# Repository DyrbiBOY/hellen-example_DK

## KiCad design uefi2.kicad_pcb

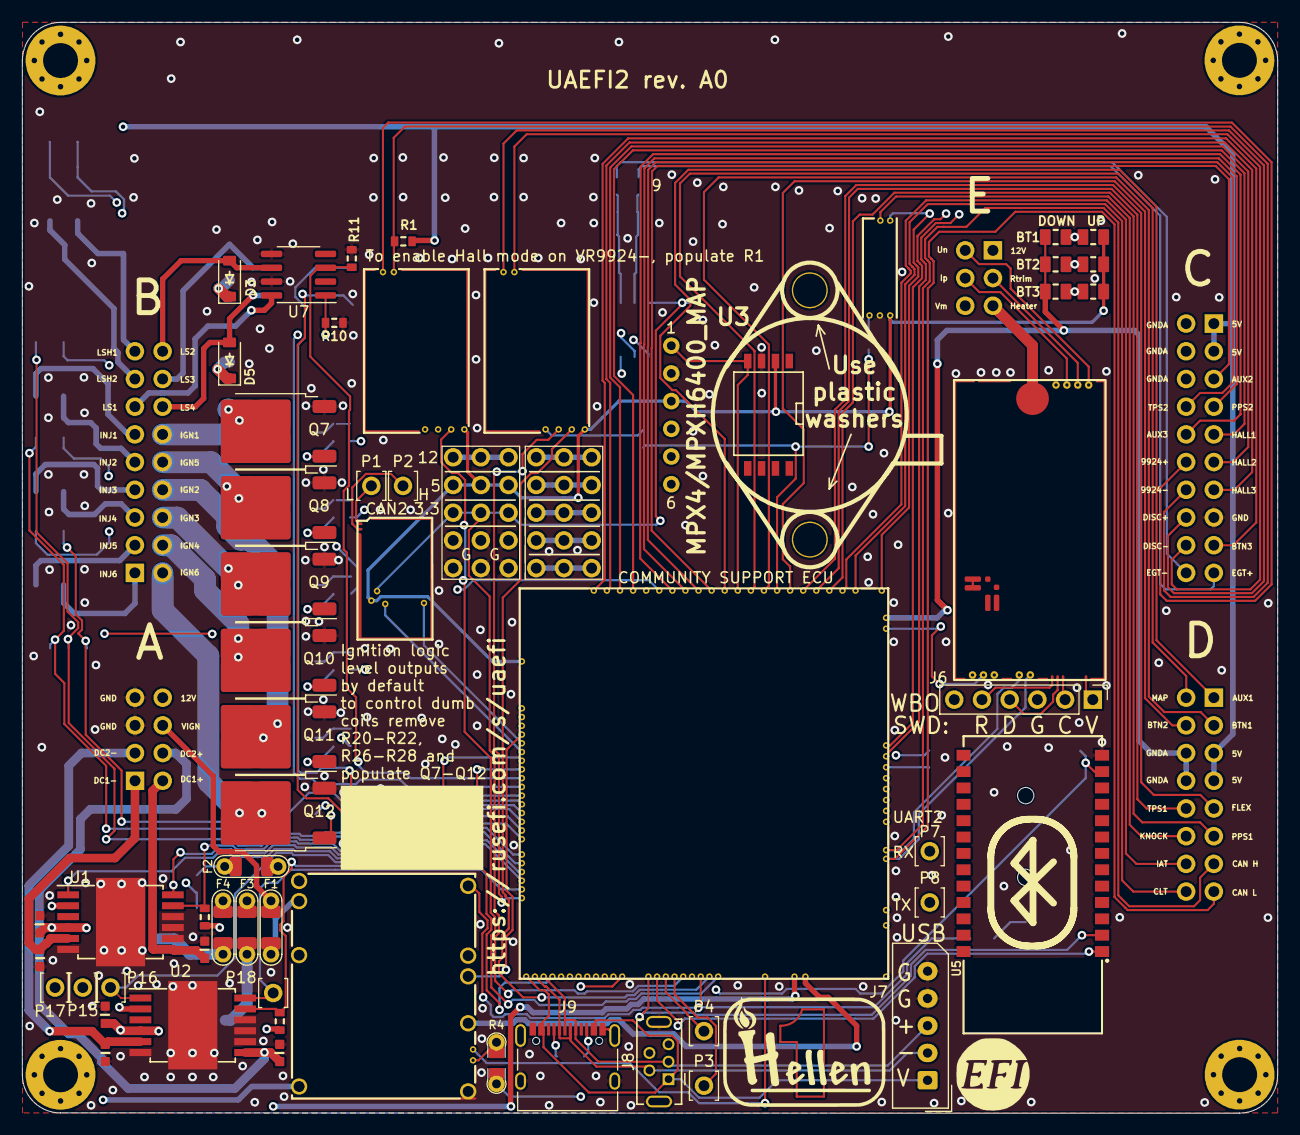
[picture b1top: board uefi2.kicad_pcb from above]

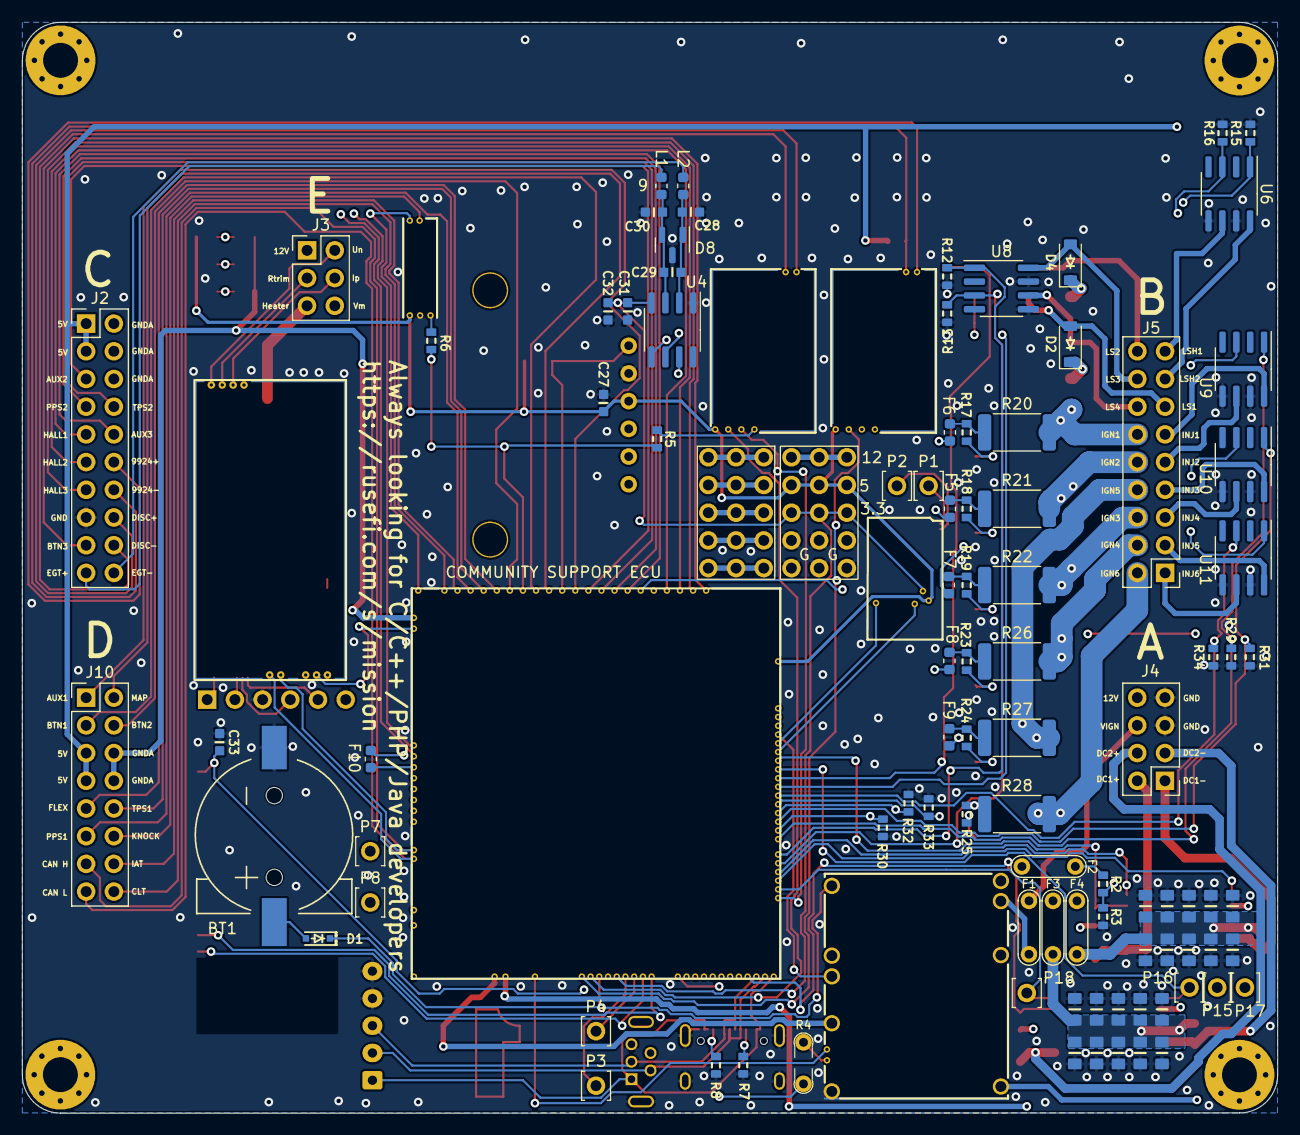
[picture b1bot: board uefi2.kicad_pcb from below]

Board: 4 copper layers, 115.1 x 100.0 mm, 143 parts (79 on the bottom side), 145 nets.

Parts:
BT1: CR1220; CR1220-2
C1, C2, C3, C4, C5, C6, C7, C8, C9, C10, C14, C15, C16, C17, C18, C19, C20, C21, C22, C23: 10u; C0805
C11, C24, C27, C29, C31, C33: 100n; C0603
C12, C13, C25, C26, C28, C30: 10n; C0603
C32: 1u; C0603
D1: 1N4148WS; SOD-323
D2, D3, D4, D5: B5819W; SOD-123
D8: NUP2105L; SOT-23
F1, F2, F3, F4: 12H1500D; PAD-1206-PAD
F5, F6, F7, F8, F9, F10: 50mA; Fuse_0603_1608Metric
G1: RUSEFI_LOGO; rusefi_logo
G2: LOGO
G3, G4: PROTO_AREA
H1, H1#2, H1#3, H2: M3; MountingHole_3.2mm_M3_Pad_Via
J2: Conn_02x10_Odd_Even; PinHeader_2x10_P2.54mm_Vertical
J3: Conn_02x03_Odd_Even; PinHeader_2x03_P2.54mm_Vertical
J4: Conn_02x04_Odd_Even; PinHeader_2x04_P2.54mm_Vertical
J5: Conn_02x09_Odd_Even; PinHeader_2x09_P2.54mm_Vertical
J6: Conn_01x06; PinHeader_1x06_P2.54mm_Vertical
J7: Conn_01x05_Male; Molex_SPOX_5267-05A_1x05_P2.50mm_Vertical
J8: USB_B_Mini; USB-MINI-B-VERTICAL
J9: USB_C
J10: Conn_02x08_Odd_Even; PinHeader_2x08_P2.54mm_Vertical
L1, L2: 470R@100MHz; L_0603_1608Metric
M1: Module-power_12and5V-0.2; power_12and5V
M2: Module-knock-0.2; knock
M3: Module-vr-discrete-0.5; vr-discrete
M4: Module-vr-max9924-0.1; vr-max9924
M5: Module-wbo-0.5; wbo
M6: Module:mega-mcu100/0.3; mega-mcu100
M7: Module-can-0.1; can
P1, P2, P3, P4, P7, P8, P15, P16, P17, P18: Pad; PAD-TH
Q7, Q8, Q9, Q10, Q11, Q12: ISL9V3040D3ST; TO-252-2
R1, R9, R10, R11, R12, R13, R14, R15, R16, R29, R30, R31, R32, R33, R34: 4.7k; R0603
R2: 33k; R0603
R3: 6.8k; R0603
R4: Jumper-Pad-Pad; PAD-0805-PAD
R5, R6: 0; R0603
R7, R8: 5.6k; R0603
R17, R18, R19, R23, R24, R25: 22; R0603
R20, R21, R22, R26, R27, R28: 0; R_2512_6332Metric
R35, R36, R37: 10k; R0805
R38, R39, R40: DNP; R0805
U1, U2: TLE9201SG; Infineon_PG-DSO-12-11
U3: MPX4/MPXH6400_MAP; MPX-4_MAP
U4: MAX31855KASA; SOIC-8_3.9x4.9mm_P1.27mm
U5: JDY-33
U6, U7, U8, U9, U10, U11: VNLD5160TR-E; SOIC-8_3.9x4.9mm_P1.27mm

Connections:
+3.3V: M6.N21 (V33), R9.2, R14.2, U1.2 (VSO), U2.2 (VSO)
+3.3VA: C31.2, C32.2, C33.2, G3.3, G3.8, G3.13, M6.N15 (V33_SWITCHABLE), M7.V2 (CAN_VIO), U4.4 (V_CC), U5.12 (3V3)
+5V: M1.E4 (V5), M6.N22 (VCC)
+5VA: C27.2, G3.4, G3.9, G3.14, M2.E1 (V5A), M3.E4 (V5_IN), M4.E4 (V5_IN), M5.W1 (V5_IN), M6.E1 (V5A_SWITCHABLE), M6.W2 (V5A_SWITCHABLE), M7.V1 (V5), R38.2, R39.2, R40.2, U3.3 (VCC)
+5VP: J2.1, J2.3, J10.5, J10.7, M1.V4 (5VP), R1.1
+12V: F2.1, F3.1, F4.1, J4.8, R2.2
+12V_RAW: D2.1 (K), D3.1 (K), D4.1 (K), D5.1 (K), F2.2, G3.5, G3.10, G3.15, J3.1, M1.V1 (V12_PERM), M1.V3 (V12_RAW)
/12V_KEY: F1.1, J4.6
/ADC3: M6.S15 (IN_KNOCK_(PA2)), R5.2, R6.2
/CAN+: J10.13, M5.W4 (CANH), M6.W11 (CANH)
/CAN-: J10.15, M5.W3 (CANL), M6.W12 (CANL)
/DC1_DIR: M6.E21 (OUT_PWM4_(PC8)), P15.1, U1.1 (DIR)
/DC1_DIS: M6.E8 (SPI2_MISO_(PB14)), R9.1, U1.11 (DIS)
/DC1_PWM: M6.E20 (OUT_PWM3_(PC7)), P17.1, U1.12 (PWM)
/DC2_DIR: M6.E9 (SPI2_MOSI_(PB15)), P16.1, U2.1 (DIR)
/DC2_DIS: M6.N4 (USBID_(PA10)), R14.1, U2.11 (DIS)
/DC2_PWM: M6.E22 (OUT_PWM5_(PC9)), P18.1, U2.12 (PWM)
/DC Driver 1/PWR: C1.2, C2.2, C3.2, C4.2, C5.2, C6.2, C7.2, C8.2, C9.2, C10.2, C11.2, F4.2, U1.4 (VS)
/DC Driver 2/PWR: C14.2, C15.2, C16.2, C17.2, C18.2, C19.2, C20.2, C21.2, C22.2, C23.2, C24.2, F3.2, U2.4 (VS)
/EGT+: J2.19, L1.1
/EGT-: J2.20, L2.1
/EGT/SPI_CS: M6.N9 (SPI3_CS_(PA15)), U4.6 (~CS)
/EGT/SPI_SCK: M6.N10 (SPI3_SCK_(PC10)), U4.5 (SCK)
/EGT/SPI_SO: M6.N11 (SPI3_MISO_(PC11)), U4.7 (SO)
/IGN1: F6.2, M6.W10 (IGN1_(PC13))
/IGN2: F5.2, M6.W9 (IGN2_(PE5))
/IGN3: F7.2, M6.W8 (IGN3_(PE4))
/IGN4: F8.2, M6.W7 (IGN4_(PE3))
/IGN5: F9.2, M6.W6 (IGN5_(PE2))
/IGN6: F10.2, M6.W5 (IGN6_(PB8))
/INJ1: M6.E17 (OUT_INJ1_(PD3)), R29.2, U9.1 (IN1)
/INJ2: M6.E16 (OUT_INJ2_(PA9)), R30.2, U9.3 (IN2)
/INJ3: M6.E15 (OUT_INJ3_(PD11)), R31.2, U10.1 (IN1)
/INJ4: M6.E14 (OUT_INJ4_(PD10)), R32.2, U10.3 (IN2)
/INJ5: M6.E13 (OUT_INJ5_(PD2)), R33.2, U11.1 (IN1)
/INJ6: M6.E12 (OUT_INJ6_(PA8)), R34.2, U11.3 (IN2)
/INTERNAL_MAP: M6.S12 (IN_MAP2_(PC1)), U3.1 (VOUT)
/IN_AUX1: J10.1, M6.S11 (IN_O2S_/_CAN_WAKEUP_(PA0))
/IN_AUX2: J2.5, M6.S10 (IN_O2S2_(PA1))
/IN_AUX3: J2.10, M6.S7 (IN_AUX3_(PA7))
/IN_BUTTON1: J10.3, M6.S14 (IN_CRANK_(PB1)), R35.2, R38.1
/IN_BUTTON2: J10.4, M6.S16 (IN_CAM_(PA6)), R36.2, R39.1
/IN_BUTTON3: J2.17, M6.S1 (IN_D4_(PE15)), R37.2, R40.1
/IN_CLT: J10.16, M6.S21 (IN_CLT_(PC2))
/IN_FLEX: J10.9, M6.S17 (IN_VSS_(PE11))
/IN_HALL1: J2.9, M6.S4 (IN_D1_(PE12))
/IN_HALL2: J2.11, M6.S3 (IN_D2_(PE13))
/IN_HALL3: J2.13, M6.S2 (IN_D3_(PE14))
/IN_IAT: J10.14, M6.S20 (IN_IAT_(PC3))
/IN_KNOCK: M2.E3 (OUT_KNOCK), R6.1
/IN_KNOCK_RAW: J10.12, M2.W1 (IN_KNOCK)
/IN_MAP: J10.2, M6.S13 (IN_MAP1_(PC0))
/IN_PPS1: J10.11, M6.S19 (IN_PPS_(PA3))
/IN_PPS2: J2.7, M6.S8 (IN_AUX2_(PC4/PE9))
/IN_TPS1: J10.10, M6.S18 (IN_TPS_(PA4))
/IN_TPS2: J2.8, M6.S9 (IN_AUX1_(PB0))
/IN_VIGN: F1.2, M1.V2 (IN_VIGN)
/IN_VMAIN: M6.S6 (IN_AUX4_(PC5)), R2.1, R3.2
/LS1: M6.E11 (OUT_INJ7_(PD15)), R10.2, U7.1 (IN1)
/LS2: M6.E10 (OUT_INJ8_(PD12)), R11.2, U7.3 (IN2)
/LS3: M6.E18 (OUT_PWM1_(PD13)), R12.2, U8.1 (IN1)
/LS4: M6.E19 (OUT_PWM2_(PC6)), R13.2, U8.3 (IN2)
/LS_HOT1: M6.W4 (IGN7_(PB9)), R16.1, U6.3 (IN2)
/LS_HOT2: M6.W3 (IGN8_(PE6)), R15.1, U6.1 (IN1)
/OUT_DC1+: C13.2, J4.2, U1.7 (OUT2)
/OUT_DC1-: C12.2, J4.1, U1.5 (OUT1)
/OUT_DC2+: C26.2, J4.4, U2.7 (OUT2)
/OUT_DC2-: C25.2, J4.3, U2.5 (OUT1)
/OUT_IGN1: J5.12, Q7.2 (C), R20.2
/OUT_IGN2: J5.10, Q8.2 (C), R21.2
/OUT_IGN3: J5.6, Q9.2 (C), R22.2
/OUT_IGN4: J5.4, Q10.2 (C), R26.2
/OUT_IGN5: J5.8, Q11.2 (C), R27.2
/OUT_IGN6: J5.2, Q12.2 (C), R28.2
/OUT_INJ1: J5.11, U9.8 (D1)
/OUT_INJ2: J5.9, U9.6 (D2)
/OUT_INJ3: J5.7, U10.8 (D1)
/OUT_INJ4: J5.5, U10.6 (D2)
/OUT_INJ5: J5.3, U11.8 (D1)
/OUT_INJ6: J5.1, U11.6 (D2)
/OUT_LS1: D2.2 (A), J5.13, U7.8 (D1)
/OUT_LS2: D3.2 (A), J5.18, U7.6 (D2)
/OUT_LS3: D4.2 (A), J5.16, U8.8 (D1)
/OUT_LS4: D5.2 (A), J5.14, U8.6 (D2)
/OUT_LS_HOT1: J5.17, U6.6 (D2)
/OUT_LS_HOT2: J5.15, U6.8 (D1)
/PG_5VP: M6.N12 (SPI3_MOSI_(PC12)), R4.2
/PWR_EN: M1.E5 (EN_5VP), M6.N20 (OUT_PWR_EN_(PE10))
/USB+: J7.3, J8.3 (D+), J9.A6 (D+), J9.B6 (D+), M6.N3 (USBP_(PA12))
/USB-: J7.2, J8.2 (D-), J9.A7 (D-), J9.B7 (D-), M6.N2 (USBM_(PA11))
/VBAT: D1.1 (K), M1.E1 (VBAT), M6.N17 (VBAT)
/VBUS: J7.1, J8.1 (VBUS), J9.A4 (VBUS), J9.A9 (VBUS), J9.B4 (VBUS), J9.B9 (VBUS), M6.N1 (VBUS)
/VIGN: M1.E3 (VIGN), M6.E5 (IN_VIGN_(PA5))
/VREF1: M2.W2 (VREF), M6.S22 (VREF1)
/VR_DISCRETE: M3.E3 (OUT), M6.N18 (UART8_RX_(PE0))
/VR_DISCRETE+: J2.16, M3.W2 (VR+)
/VR_DISCRETE-: J2.18, M3.W1 (VR-)
/VR_DISCRETE_A: M3.E2 (OUT_A), R5.1
/VR_DISCRETE_THR: M3.E1 (Thresh_IN), M6.E23 (OUT_PWM6_(PD14))
/VR_MAX9924: M4.E3 (OUT), M6.N19 (UART8_TX_(PE1))
/VR_MAX9924+: J2.12, M4.W2 (VR+)
/VR_MAX9924-: J2.14, M4.W1 (VR-), R1.2
/WBO_Heater: J3.5, M5.E5 (LSU_H+)
/WBO_Ip: J3.4, M5.E3 (LSU_Ip)
/WBO_Rtrim: J3.3, M5.E4 (LSU_Rtrim)
/WBO_Un: J3.2, M5.E1 (LSU_Un)
/WBO_Vm: J3.6, M5.E2 (LSU_Vm)
GND: BT1.2 (-), C1.1, C2.1, C3.1, C4.1, C5.1, C6.1, C7.1, C8.1, C9.1, C10.1, C11.1, C12.1, C13.1, C14.1, C15.1, C16.1, C17.1, C18.1, C19.1, C20.1, C21.1, C22.1, C23.1, C24.1, C25.1, C26.1, C27.1, C28.1, C30.1, C31.1, C32.1, C33.1, D8.3 (A), G3.1, G3.2, G3.6, G3.7, G3.11, G3.12, J2.15, J4.5, J4.7, J6.3, J7.4, J7.5, J8.5 (GND), J8.6 (Shield), J9.A1 (GND), J9.A12 (GND), J9.B1 (GND), J9.B12 (GND), J9.S1 (SHIELD), M1.S1 (GND), M2.E2 (GND), M3.G (GND), M4.G (GND), M5.E6 (LSU_H-), M5.G (GND), M6.G (GND), M7.E1 (GND), Q7.3 (E), Q8.3 (E), Q9.3 (E), Q10.3 (E), Q11.3 (E), Q12.3 (E), R3.1, R7.1, R8.1, R10.1, R11.1, R12.1, R13.1, R15.2, R16.2, R29.1, R30.1, R31.1, R32.1, R33.1, R34.1, U1.6 (GND), U1.8 (SI), U1.9 (CSN), U1.10 (SCK), U1.13 (GND), U2.6 (GND), U2.8 (SI), U2.9 (CSN), U2.10 (SCK), U2.13 (GND), U3.2 (GND), U4.1 (GND), U5.13 (GND), U6.5 (S2), U6.7 (S1), U7.5 (S2), U7.7 (S1), U8.5 (S2), U8.7 (S1), U9.5 (S2), U9.7 (S1), U10.5 (S2), U10.7 (S1), U11.5 (S2), U11.7 (S1)
GNDA: J2.2, J2.4, J2.6, J10.6, J10.8, M6.W1 (GNDA), R35.1, R36.1, R37.1
unnamed: BT1.1 (+), D1.2 (A)
unnamed: F5.1, R18.2, R21.1
unnamed: F6.1, R17.2, R20.1
unnamed: F7.1, R19.2, R22.1
unnamed: F8.1, R23.2, R26.1
unnamed: F9.1, R24.2, R27.1
unnamed: F10.1, R25.2, R28.1
unnamed: G4.1, G4.6, G4.11
unnamed: G4.5, G4.10, G4.15
unnamed: G4.2, G4.7, G4.12
unnamed: G4.3, G4.8, G4.13
unnamed: G4.4, G4.9, G4.14
unnamed: J6.1, M5.W8 (V33_OUT)
unnamed: J6.2, M5.W7 (SWCLK)
unnamed: J6.4, M5.W6 (SWDIO)
unnamed: J6.5, M5.W5 (nReset)
unnamed: J9.A5 (CC1), R7.2
unnamed: J9.B5 (CC2), R8.2
unnamed: M1.E6 (PG_5VP), R4.1
unnamed: M5.J1 (SEL1), M5.J_GND1 (PULL_DOWN1)
unnamed: M6.N14a (LED_GREEN), P4.1
unnamed: M6.N14b (LED_YELLOW), P3.1
unnamed: M6.E6 (SPI2_CS_/_CAN2_RX_(PB12)), M7.V6 (CAN_RX)
unnamed: M6.E7 (SPI2_SCK_/_CAN2_TX_(PB13)), M7.V5 (CAN_TX)
unnamed: M6.N14 (UART2_RX_(PD6)), P7.1, U5.1 (TXD)
unnamed: M6.N13 (UART2_TX_(PD5)), P8.1, U5.2 (RXD)
unnamed: M7.S2 (CANH), P2.1
unnamed: M7.S1 (CANL), P1.1
unnamed: Q7.1 (G), R17.1
unnamed: Q8.1 (G), R18.1
unnamed: Q9.1 (G), R19.1
unnamed: Q10.1 (G), R23.1
unnamed: Q11.1 (G), R24.1
unnamed: Q12.1 (G), R25.1
unnamed: C29.2, C30.2, D8.2 (K), L1.2, U4.3 (T+)
unnamed: C28.2, C29.1, D8.1 (K), L2.2, U4.2 (T-)

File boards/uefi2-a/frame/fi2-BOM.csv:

Comment,Designator,Footprint,LCSC Part #
"CR1220","BT1","CR1220-2","C70381"
"10u","C1","C0805","C15850"
"10u","C2","C0805","C15850"
"10u","C3","C0805","C15850"
"10u","C4","C0805","C15850"
"10u","C5","C0805","C15850"
"10u","C6","C0805","C15850"
"10u","C7","C0805","C15850"
"10u","C8","C0805","C15850"
"10u","C9","C0805","C15850"
"10u","C10","C0805","C15850"
"100n","C11","C0603","C14663"
"10n","C12","C0603","C57112"
"10n","C13","C0603","C57112"
"10u","C14","C0805","C15850"
"10u","C15","C0805","C15850"
"10u","C16","C0805","C15850"
"10u","C17","C0805","C15850"
"10u","C18","C0805","C15850"
"10u","C19","C0805","C15850"
"10u","C20","C0805","C15850"
"10u","C21","C0805","C15850"
"10u","C22","C0805","C15850"
"10u","C23","C0805","C15850"
"100n","C24","C0603","C14663"
"10n","C25","C0603","C57112"
"10n","C26","C0603","C57112"
"100n","C27","C0603","C14663"
"10n","C28","C0603","C57112"
"100n","C29","C0603","C14663"
"10n","C30","C0603","C57112"
"100n","C31","C0603","C14663"
"1u","C32","C0603","C15849"
"100n","C33","C0603","C14663"
"1N4148WS","D1","SOD-323","C2128"
"B5819W","D2","SOD-123","C8598"
"B5819W","D3","SOD-123","C8598"
"B5819W","D4","SOD-123","C8598"
"B5819W","D5","SOD-123","C8598"
"NUP2105L","D8","SOT-23","C284104"
"12H1500D","F1","PAD-1206-PAD","C182446"
"12H1500D","F2","PAD-1206-PAD","C182446"
"12H1500D","F3","PAD-1206-PAD","C182446"
"12H1500D","F4","PAD-1206-PAD","C182446"
"50mA","F5","Fuse_0603_1608Metric","C369141"
"50mA","F6","Fuse_0603_1608Metric","C369141"
"50mA","F7","Fuse_0603_1608Metric","C369141"
"50mA","F8","Fuse_0603_1608Metric","C369141"
"50mA","F9","Fuse_0603_1608Metric","C369141"
"50mA","F10","Fuse_0603_1608Metric","C369141"
"RUSEFI_LOGO","G1","rusefi_logo",""
"LOGO","G2","LOGO",""
"PROTO_AREA","G3","PROTO_AREA",""
"PROTO_AREA","G4","PROTO_AREA",""
"M3","H1","MountingHole_3.2mm_M3_Pad_Via",""
"M3","H2","MountingHole_3.2mm_M3_Pad_Via",""
"M3","H3","MountingHole_3.2mm_M3_Pad_Via",""
"M3","H4","MountingHole_3.2mm_M3_Pad_Via",""
"Conn_02x10_Odd_Even","J2","PinHeader_2x10_P2.54mm_Vertical","C5789508"
"Conn_02x03_Odd_Even","J3","PinHeader_2x03_P2.54mm_Vertical","C41375945"
"Conn_02x04_Odd_Even","J4","PinHeader_2x04_P2.54mm_Vertical","C7501595"
"Conn_02x09_Odd_Even","J5","PinHeader_2x09_P2.54mm_Vertical","C27985168"
"Conn_01x06","J6","PinHeader_1x06_P2.54mm_Vertical","C37208"
"Conn_01x05_Male","J7","Molex_SPOX_5267-05A_1x05_P2.50mm_Vertical",""
"USB_B_Mini","J8","USB-MINI-B-VERTICAL",""
"USB_C","J9","USB_C","C2927038"
"Conn_02x08_Odd_Even","J10","PinHeader_2x08_P2.54mm_Vertical","C41375949"
"470R@100MHz","L1","L_0603_1608Metric","C97853"
"470R@100MHz","L2","L_0603_1608Metric","C97853"
"Module:power_12and5V/0.2","M1","power_12and5V",""
"Module:knock/0.2","M2","knock",""
"Module:vr-discrete/0.5","M3","vr-discrete",""
"Module:vr-max9924/0.1","M4","vr-max9924",""
"Module:wbo/0.5","M5","wbo",""
"Module:mega-mcu100/0.3","M6","mega-mcu100",""
"Module:can/0.1","M7","can",""
"Pad","P1","PAD-TH",""
"Pad","P2","PAD-TH",""
"Pad","P3","PAD-TH",""
"Pad","P4","PAD-TH",""
"Pad","P7","PAD-TH",""
"Pad","P8","PAD-TH",""
"Pad","P15","PAD-TH",""
"Pad","P16","PAD-TH",""
"Pad","P17","PAD-TH",""
"Pad","P18","PAD-TH",""
"ISL9V3040D3ST","Q7","DPAK",""
"ISL9V3040D3ST","Q8","DPAK",""
"ISL9V3040D3ST","Q9","DPAK",""
"ISL9V3040D3ST","Q10","DPAK",""
"ISL9V3040D3ST","Q11","DPAK",""
"ISL9V3040D3ST","Q12","DPAK",""
"4.7k","R1","R0603",""
"33k","R2","R0603","C4216"
"6.8k","R3","R0603","C23212"
"Jumper-Pad-Pad","R4","PAD-0805-PAD","C17477"
"0","R5","R0603",""
"0","R6","R0603","C21189"
"5.6k","R7","R0603","C23189"
"5.6k","R8","R0603","C23189"
"4.7k","R9","R0603","C23162"
"4.7k","R10","R0603","C23162"
"4.7k","R11","R0603","C23162"
"4.7k","R12","R0603","C23162"
"4.7k","R13","R0603","C23162"
"4.7k","R14","R0603","C23162"
"4.7k","R15","R0603","C23162"
"4.7k","R16","R0603","C23162"
"22","R17","R0603","C23345"
"22","R18","R0603","C23345"
"22","R19","R0603","C23345"
"0","R20","R2512","C25469"
"0","R21","R2512","C25469"
"0","R22","R2512","C25469"
"22","R23","R0603","C23345"
"22","R24","R0603","C23345"
"22","R25","R0603","C23345"
"0","R26","R2512","C25469"
"0","R27","R2512","C25469"
"0","R28","R2512","C25469"
"4.7k","R29","R0603","C23162"
"4.7k","R30","R0603","C23162"
"4.7k","R31","R0603","C23162"
"4.7k","R32","R0603","C23162"
"4.7k","R33","R0603","C23162"
"4.7k","R34","R0603","C23162"
"10k","R35","R0805","C17414"
"10k","R36","R0805","C17414"
"10k","R37","R0805","C17414"
"DNP","R38","R0805",""
"DNP","R39","R0805",""
"DNP","R40","R0805",""
"TLE9201SG","U1","Infineon_PG-DSO-12-11","C112633"
"TLE9201SG","U2","Infineon_PG-DSO-12-11","C112633"
"MPX4/MPXH6400_MAP","U3","MPX-4_MAP",""
"MAX31855KASA","U4","SO8","C52028"
"JDY-33","U5","JDY-33","C9900001612"
"VNLD5160TR-E","U6","SO8","C377942"
"VNLD5160TR-E","U7","SO8","C377942"
"VNLD5160TR-E","U8","SO8","C377942"
"VNLD5160TR-E","U9","SO8","C377942"
"VNLD5160TR-E","U10","SO8","C377942"
"VNLD5160TR-E","U11","SO8","C377942"

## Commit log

2024-10-18 [skip actions] Auto-generated board v2.1
2024-10-18 add bom_replace_uefi2-a
2024-10-29 GHA says update hellen-one
2024-11-12 change revision from a to A0, change kicad file
2024-12-02 GHA says update kicad6-libraries
